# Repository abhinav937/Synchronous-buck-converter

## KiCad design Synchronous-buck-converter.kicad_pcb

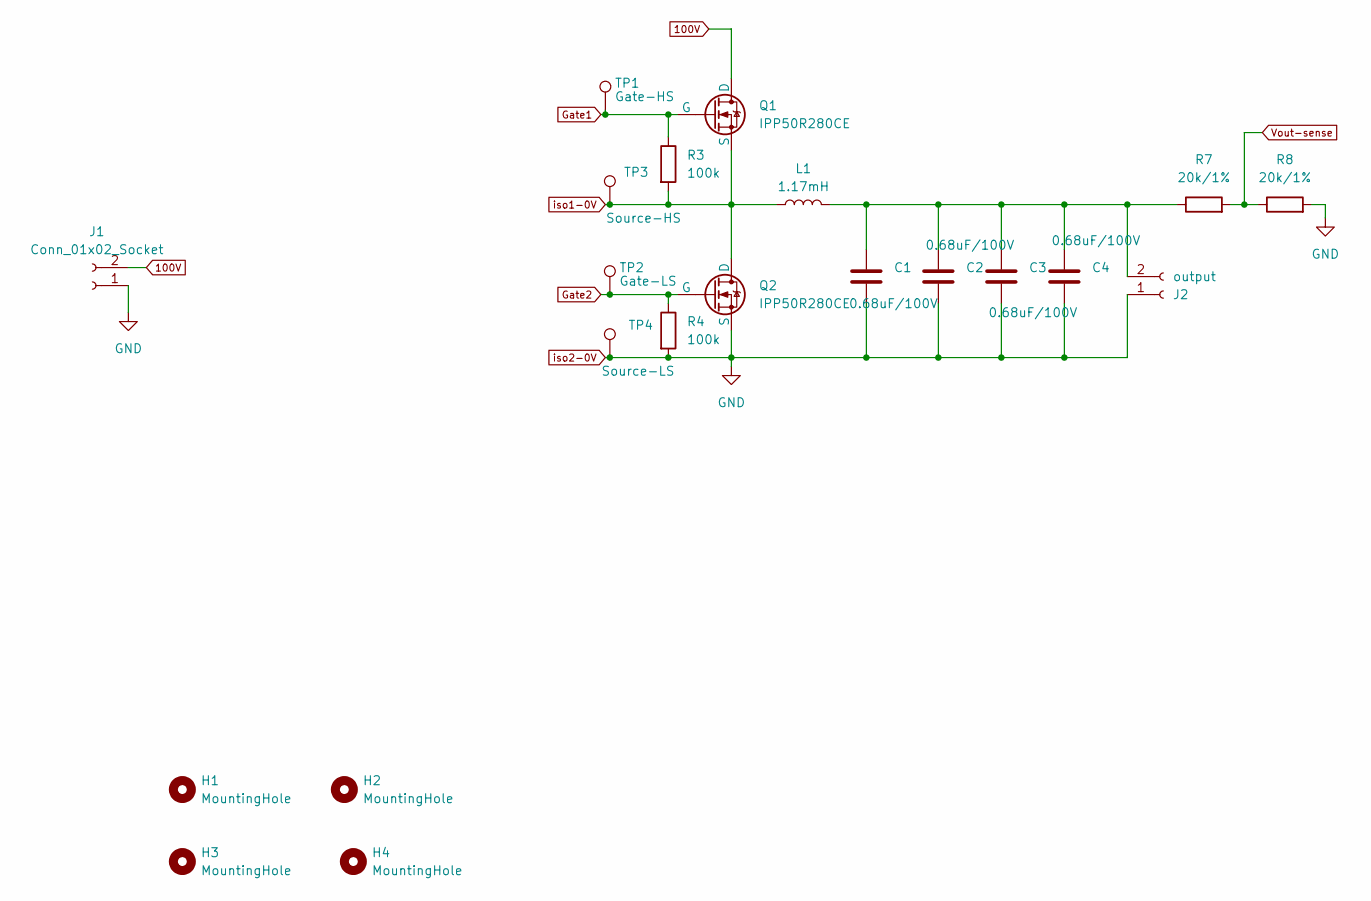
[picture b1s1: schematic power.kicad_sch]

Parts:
C1, C2, C3, C4: 0.68uF/100V; C_1812_4532Metric; mouser part no: C1812C684K1RACTU
H1, H2, H3, H4: MountingHole; MountingHole_3.2mm_M3
J1: Conn_01x02_Socket; TerminalBlock_Phoenix_MKDS-1,5-2_1x02_P5.00mm_Horizontal
J2: output; TerminalBlock_Phoenix_MKDS-1,5-2_1x02_P5.00mm_Horizontal
L1: 1.17mH; 42-21-15 bobbin
Q1, Q2: IPP50R280CE; TO-220-3_Vertical
R3, R4: 100k; R_0805_2012Metric
R7, R8: 20k/1%; R_0805_2012Metric
TP1: Gate-HS; KEYSTONE_5001
TP2: Gate-LS; KEYSTONE_5001
TP3: Source-HS; KEYSTONE_5001
TP4: Source-LS; KEYSTONE_5001

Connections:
100V: J1.2, Q1.2 (D); also elsewhere on the board
Gate1: Q1.1 (G), R3.1, TP1.1; also elsewhere on the board
Gate2: Q2.1 (G), R4.1, TP2.1; also elsewhere on the board
unnamed: C1.1, C2.1, C3.1, C4.1, J2.2, L1.2, R7.1
Vout-sense: R7.2, R8.1; also elsewhere on the board
iso1-0V: L1.1, Q1.3 (S), Q2.2 (D), R3.2, TP3.1; also elsewhere on the board
iso2-0V: C1.2, C2.2, C3.2, C4.2, J1.1, J2.1, Q2.3 (S), R4.2, R8.2, TP4.1; also elsewhere on the board

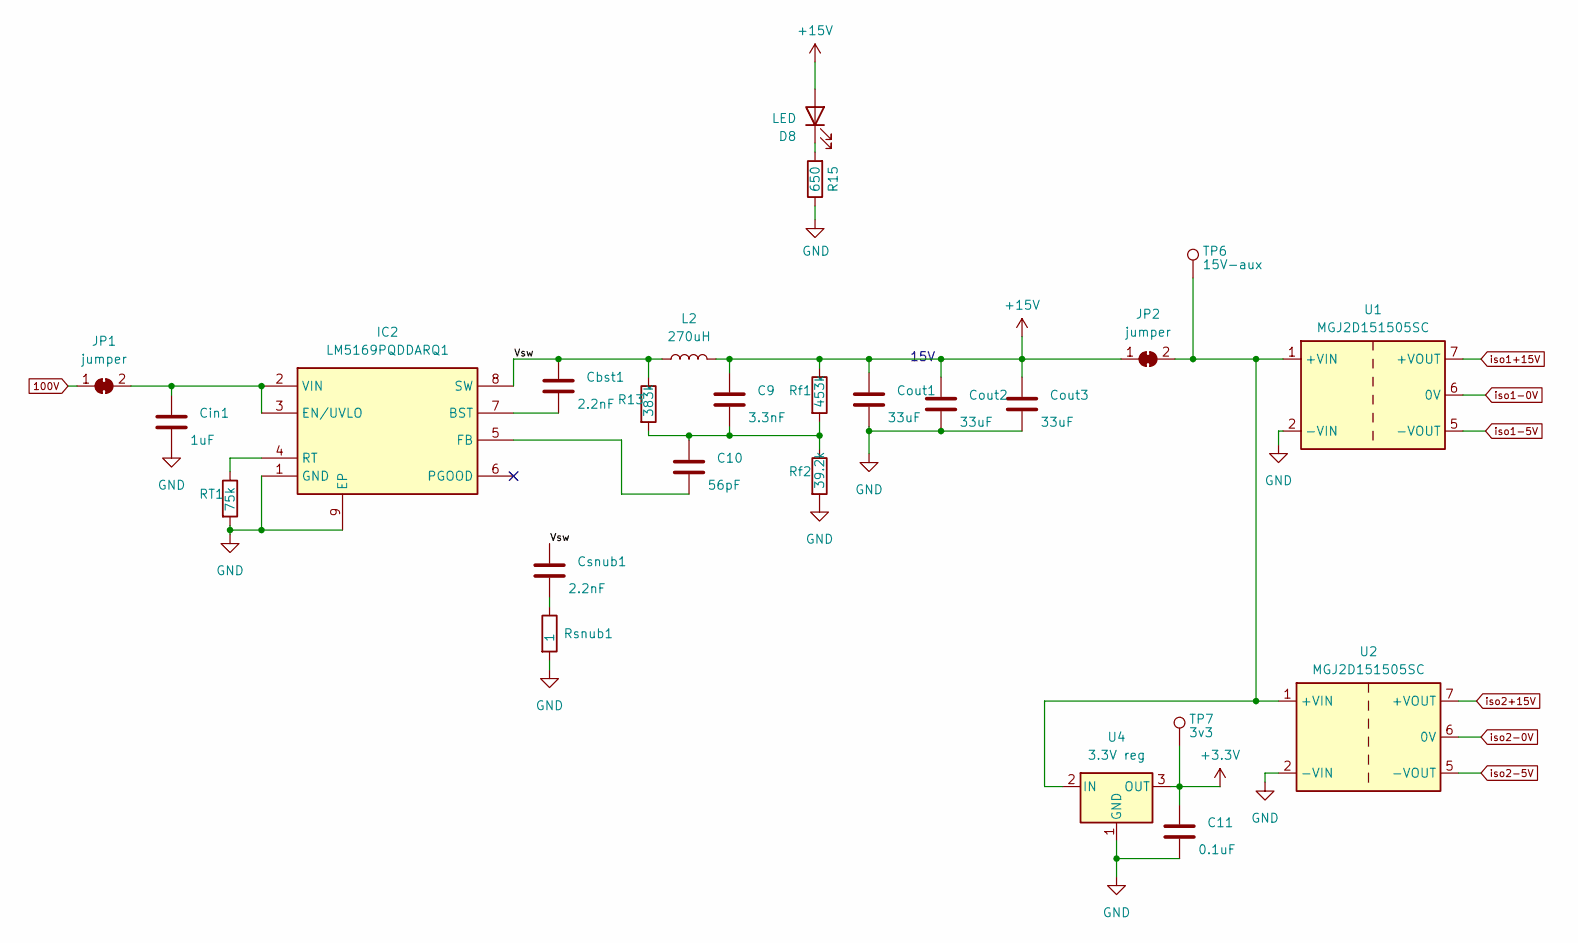
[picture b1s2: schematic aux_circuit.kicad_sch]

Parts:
C9: 3.3nF; C_0805_2012Metric
C10: 56pF; C_0805_2012Metric
C11: 0.1uF; C_0805_2012Metric
Cbst1: 2.2nF; C_0805_2012Metric
Cin1: 1uF; C_1812_4532Metric; mouser no 18122C105JAT2A
Cout1, Cout2, Cout3: 33uF; C_1210_3225Metric
Csnub1: 2.2nF; C_0805_2012Metric
D8: LED; LED_0805_2012Metric
IC2: LM5169PQDDARQ1; SOIC127P600X170-9N; Manufacturer_Part_Number LM5169PQDDARQ1; Mouser Part Number 595-LM5169PQDDARQ1
JP1, JP2: jumper; SolderJumper-2_P1.3mm_Open_RoundedPad1.0x1.5mm
L2: 270uH; INDPM102100X510N; mouser part no SRR1050HA-271Y
R13: 383k; R_0805_2012Metric
R15: 650; R_0805_2012Metric
RT1: 75k; R_0805_2012Metric
Rf1: 453k; R_0805_2012Metric
Rf2: 39.2k; R_0805_2012Metric
Rsnub1: 1; R_0805_2012Metric
TP6: 15V-aux; KEYSTONE_5001
TP7: 3v3; KEYSTONE_5001
U1, U2: MGJ2D151505SC; Converter_DCDC_Murata_MGJ2DxxxxxxSC_THT
U4: 3.3V reg; SOT-89-3; mouser part no TLV709A33PKR

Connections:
100V: JP1.1 (A); also elsewhere on the board
+3.3V: C11.1, TP7.1, U4.3 (OUT); also elsewhere on the board
+15V: C9.1, Cout1.1, Cout2.1, Cout3.1, D8.2 (A), JP2.1 (A), L2.2, Rf1.1
/auxiliary circuit/Vsw: Cbst1.1, Csnub1.1, IC2.8 (SW), L2.1, R13.1
unnamed: C9.2, C10.1, R13.2, Rf1.2, Rf2.1
unnamed: Csnub1.2, Rsnub1.1
unnamed: D8.1 (K), R15.2
unnamed: Cbst1.2, IC2.7 (BST)
unnamed: Cin1.1, IC2.2 (VIN), IC2.3 (EN/UVLO), JP1.2 (B)
unnamed: C10.2, IC2.5 (FB)
unnamed: IC2.4 (RT), RT1.1
unnamed: JP2.2 (B), TP6.1, U1.1 (+VIN), U2.1 (+VIN), U4.2 (IN)
iso1+15V: U1.7 (+VOUT); also elsewhere on the board
iso1-0V: U1.6 (0V); also elsewhere on the board
iso1-5V: U1.5 (-VOUT); also elsewhere on the board
iso2+15V: U2.7 (+VOUT); also elsewhere on the board
iso2-0V: C11.2, Cin1.2, Cout1.2, Cout2.2, Cout3.2, IC2.1 (GND), IC2.9 (EP), R15.1, RT1.2, Rf2.2, Rsnub1.2, U1.2 (-VIN), U2.2 (-VIN), U2.6 (0V), U4.1 (GND); also elsewhere on the board
iso2-5V: U2.5 (-VOUT); also elsewhere on the board

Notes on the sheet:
15V

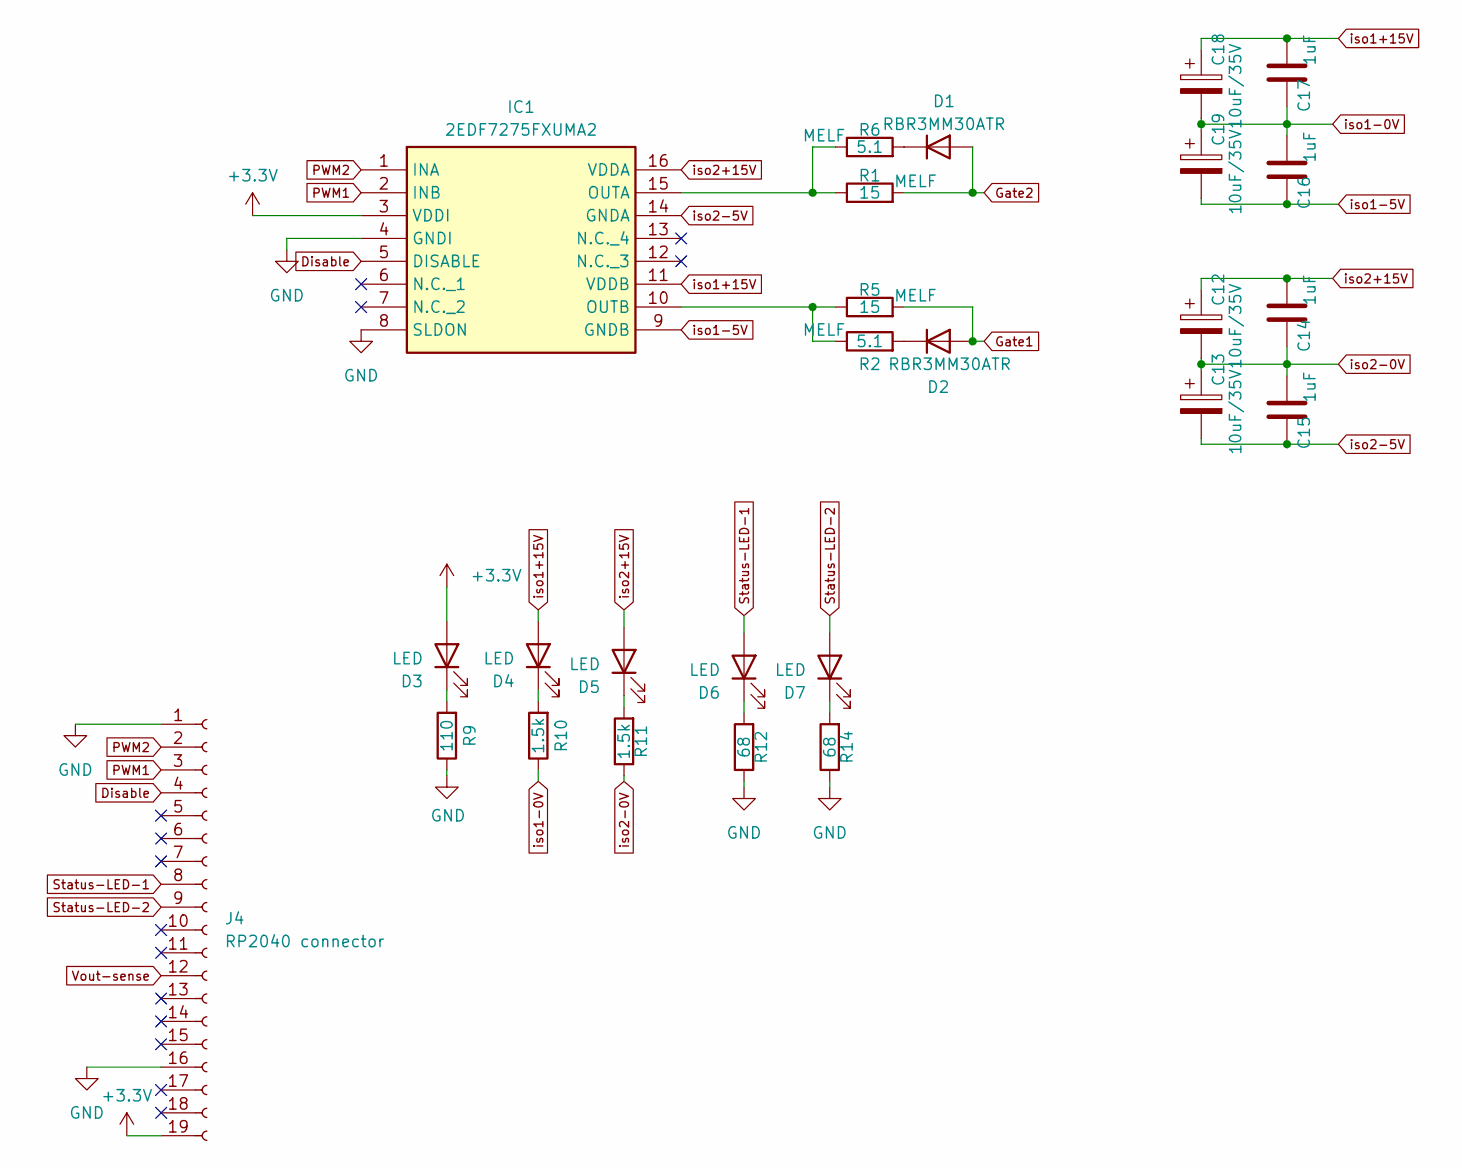
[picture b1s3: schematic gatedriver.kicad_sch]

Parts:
C12, C13, C18, C19: 10uF/35V; CP_Elec_5x5.3
C14, C15, C16, C17: 1uF; C_0805_2012Metric
D1, D2: RBR3MM30ATR; D_SOD-123F
D3, D4, D5, D6, D7: LED; LED_0805_2012Metric
IC1: 2EDF7275FXUMA2; SOIC127P600X175-16N; Manufacturer_Part_Number 2EDF7275FXUMA2; Mouser Part Number 726-2EDF7275FXUMA2
J4: RP2040 connector; PinSocket_1x19_P2.54mm_Horizontal
R1, R5: 15; R_MiniMELF_MMA-0204; mouser part no CMA02040X1509GB300
R2, R6: 5.1; R_MiniMELF_MMA-0204; mouser part no MMA02040C5108FB300
R9: 110; R_0805_2012Metric
R10, R11: 1.5k; R_0805_2012Metric
R12, R14: 68; R_0805_2012Metric

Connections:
+3.3V: D3.2 (A), IC1.3 (VDDI), J4.19; also elsewhere on the board
Disable: IC1.5 (DISABLE), J4.4
Gate1: D2.2 (A), R5.2; also elsewhere on the board
Gate2: D1.2 (A), R1.2; also elsewhere on the board
unnamed: D1.1 (K), R6.2
unnamed: D2.1 (K), R2.2
unnamed: D3.1 (K), R9.2
unnamed: D4.1 (K), R10.2
unnamed: D5.1 (K), R11.2
unnamed: D6.1 (K), R12.2
unnamed: D7.1 (K), R14.2
unnamed: IC1.15 (OUTA), R1.1, R6.1
unnamed: IC1.10 (OUTB), R2.1, R5.1
PWM1: IC1.2 (INB), J4.3
PWM2: IC1.1 (INA), J4.2
Status-LED-1: D6.2 (A), J4.8
Status-LED-2: D7.2 (A), J4.9
Vout-sense: J4.12; also elsewhere on the board
iso1+15V: C17.2, C18.1, D4.2 (A), IC1.11 (VDDB); also elsewhere on the board
iso1-0V: C16.2, C17.1, C18.2, C19.1, R10.1; also elsewhere on the board
iso1-5V: C16.1, C19.2, IC1.9 (GNDB); also elsewhere on the board
iso2+15V: C12.1, C14.2, D5.2 (A), IC1.16 (VDDA); also elsewhere on the board
iso2-0V: C12.2, C13.1, C14.1, C15.2, IC1.4 (GNDI), IC1.8 (SLDON), J4.1, J4.16, R9.1, R11.1, R12.1, R14.1; also elsewhere on the board
iso2-5V: C13.2, C15.1, IC1.14 (GNDA); also elsewhere on the board

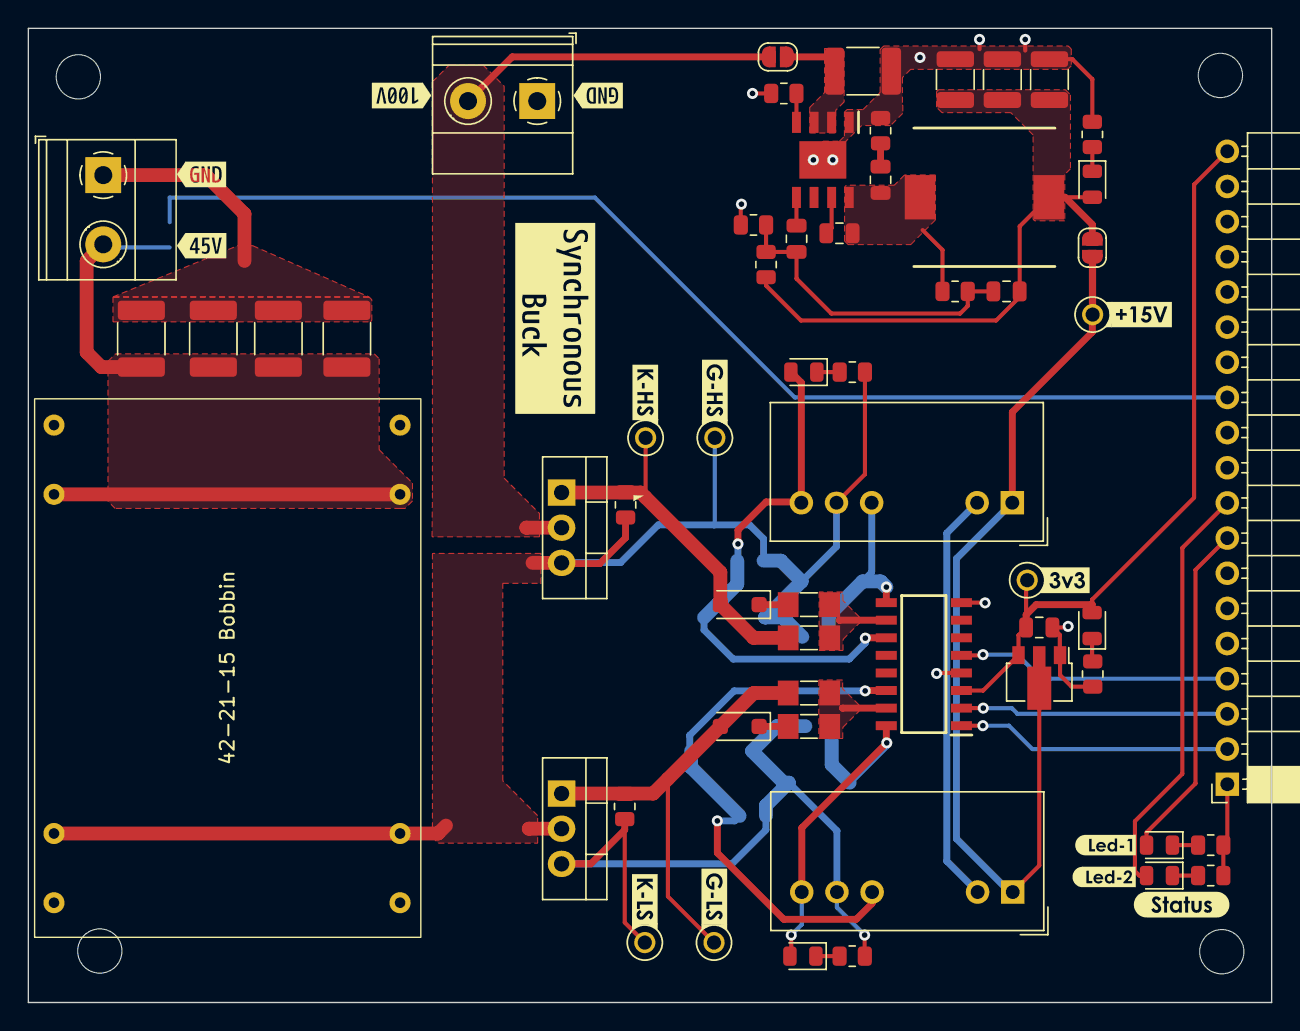
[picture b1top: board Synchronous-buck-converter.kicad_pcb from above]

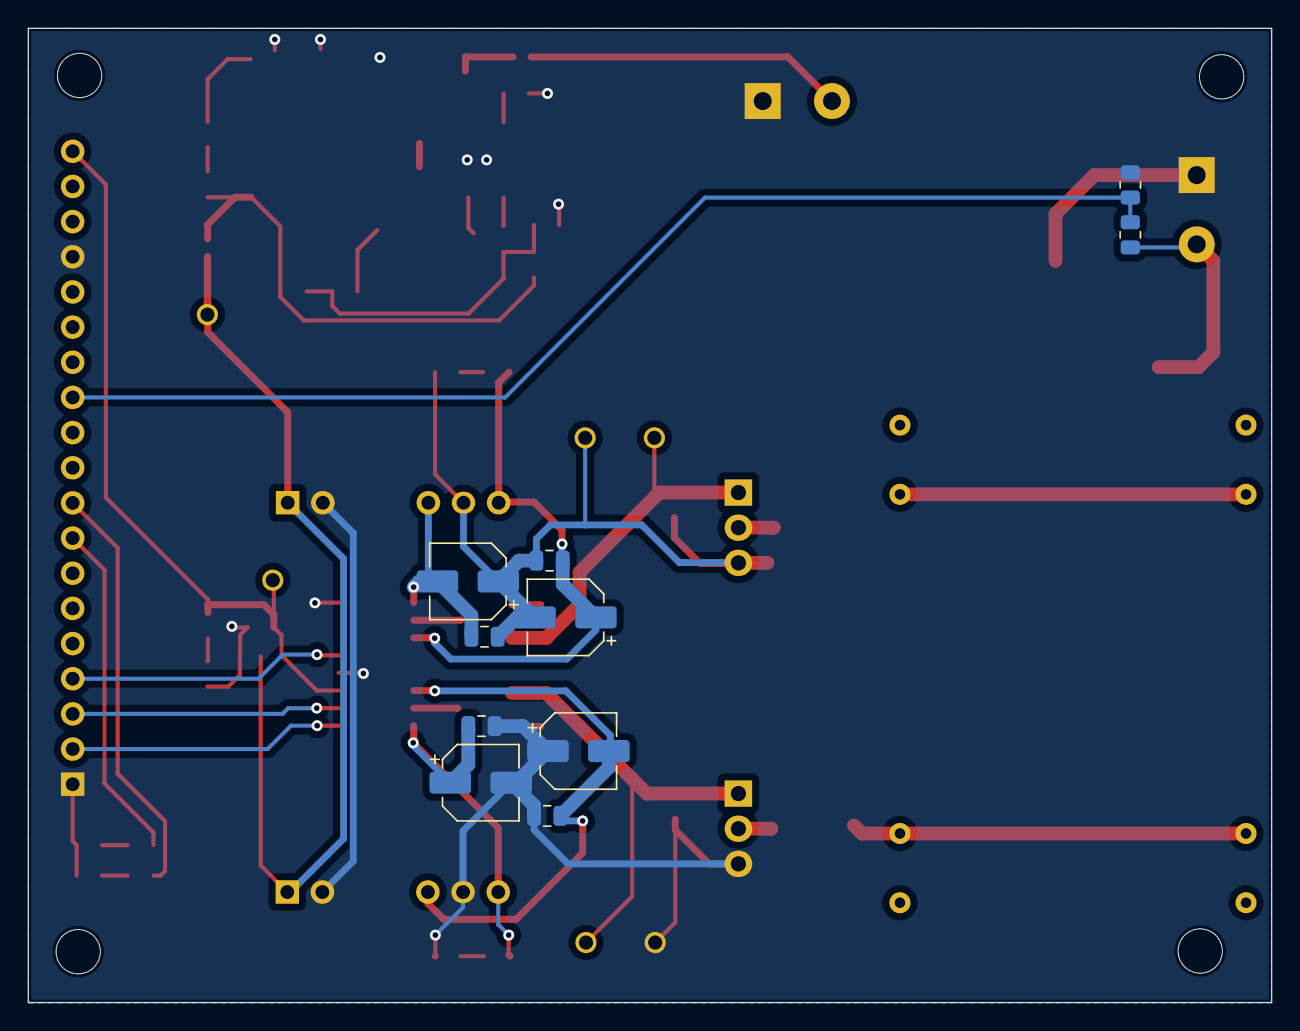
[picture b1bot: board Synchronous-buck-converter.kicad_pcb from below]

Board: 2 copper layers, 89.8 x 70.4 mm, 88 parts (10 on the bottom side), 36 nets.

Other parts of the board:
kibuzzard-65CA68FA: G***; kibuzzard-65CA68FA
kibuzzard-65CA6608: G***; kibuzzard-65CA6608
kibuzzard-65CA6684: G***; kibuzzard-65CA6684
kibuzzard-65CA6739: G***; kibuzzard-65CA6739
kibuzzard-65CA6750: G***; kibuzzard-65CA6750
kibuzzard-65CA6838: G***; kibuzzard-65CA6838
kibuzzard-65CA6847: G***; kibuzzard-65CA6847
kibuzzard-65CA6899: G***; kibuzzard-65CA6899
kibuzzard-65CA6927: G***; kibuzzard-65CA6927
kibuzzard-65F43C4A: G***; kibuzzard-65F43C4A
kibuzzard-65F43C21: G***; kibuzzard-65F43C21
kibuzzard-65F43C74: G***; kibuzzard-65F43C74
kibuzzard-65F43CE0: G***; kibuzzard-65F43CE0
kibuzzard-65F43CF3: G***; kibuzzard-65F43CF3
kibuzzard-65F4406D: G***; kibuzzard-65F4406D
kibuzzard-65F44031: G***; kibuzzard-65F44031

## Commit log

2024-02-14 drafted the schematic and layout
    Not consulted with professor yet about the design
2024-02-14 Schematic and layout drafted
    Not consulted with professor yet to proceed for routing
2024-02-14 file errors corrected
2024-03-15 V1
    layout and tracing done
2024-05-03 Full design files with codes
